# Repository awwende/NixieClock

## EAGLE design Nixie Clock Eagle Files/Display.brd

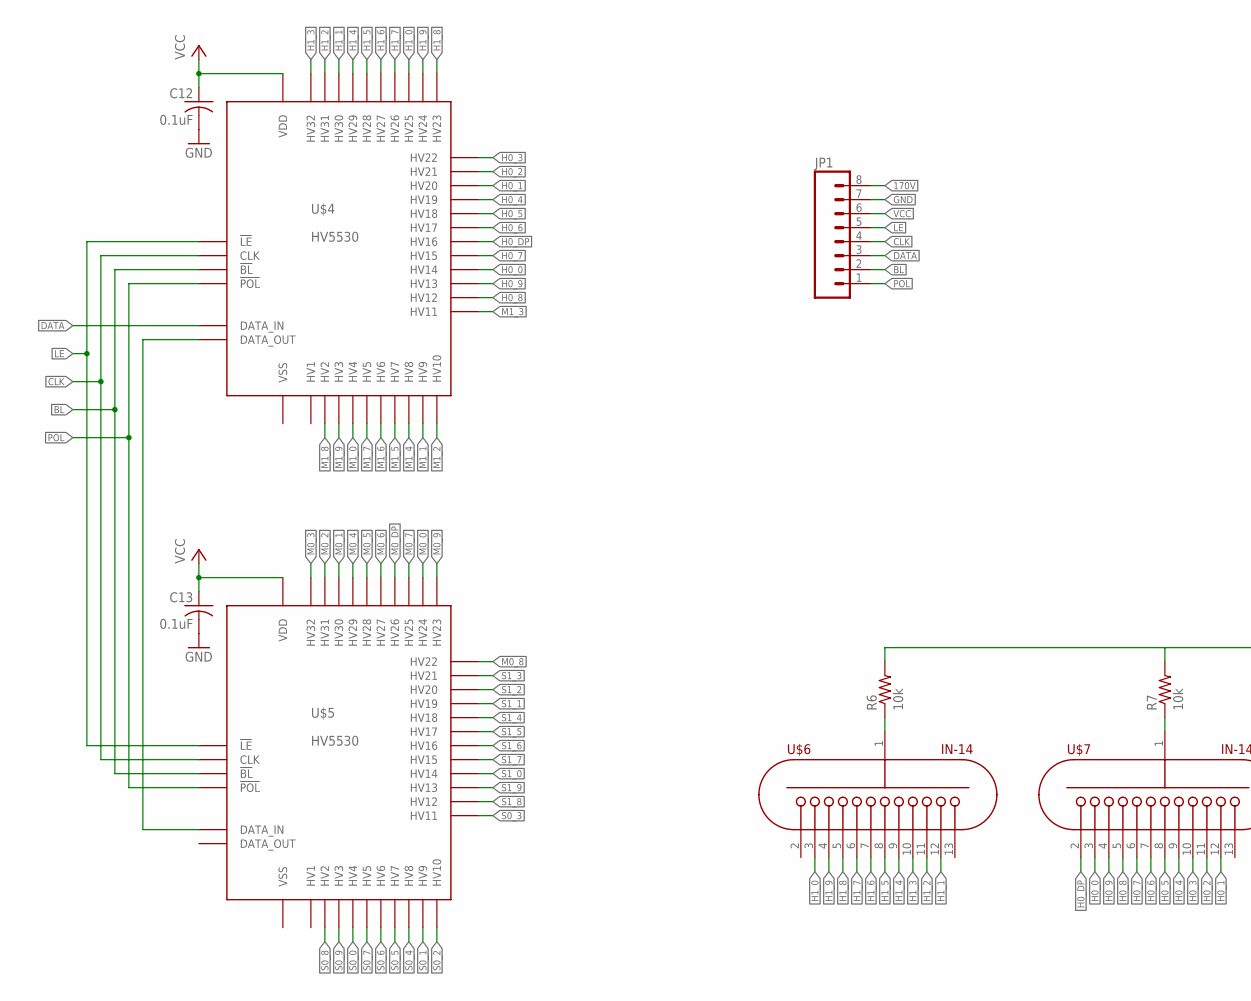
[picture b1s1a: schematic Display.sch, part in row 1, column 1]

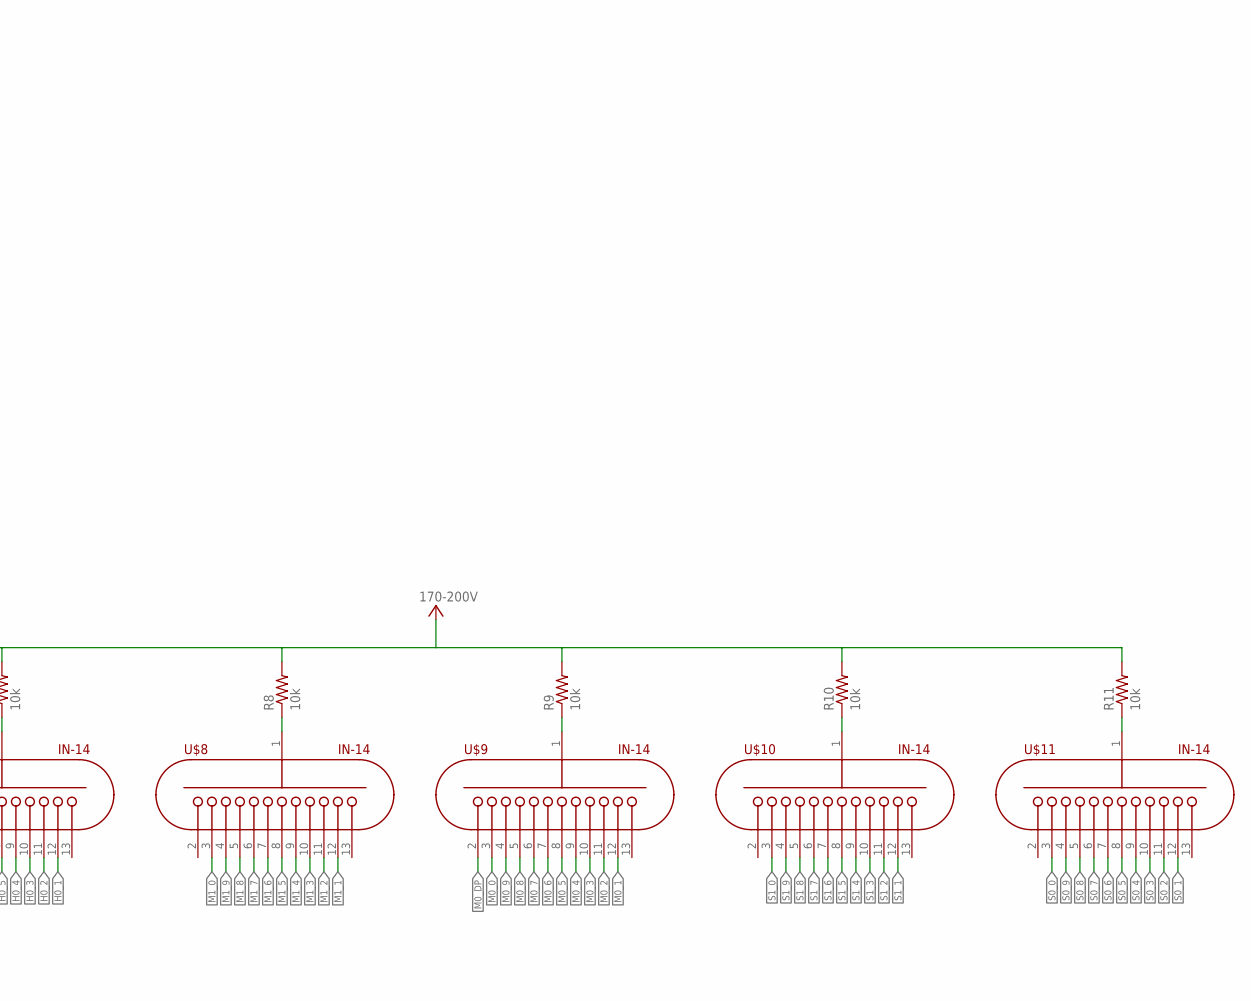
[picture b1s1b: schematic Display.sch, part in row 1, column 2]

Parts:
C12, C13: 0.1uF; C0603
JP1: M08; 1X08_PIN1_NO_SILK
R6, R7, R8, R9, R10, R11: 10k; R0603
U$4, U$5: HV5530PLCC; PLCC
U$6, U$7, U$8, U$9, U$10, U$11: IN-14

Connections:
170V: JP1.8, R6.2, R7.2, R8.2, R9.2, R10.2, R11.2
!BL: JP1.2, U$4.BL (!BL), U$5.BL (!BL)
!LE: JP1.5, U$4.LE (!LE), U$5.LE (!LE)
!POL: JP1.1, U$4.POL (!POL), U$5.POL (!POL)
CLK: JP1.4, U$4.CLK, U$5.CLK
DATA: JP1.3, U$4.D_IN (DATA_IN)
GND: C12.2, C13.2, JP1.7
H0_0: U$4.HV14, U$7.3
H0_1: U$4.HV20, U$7.12
H0_2: U$4.HV21, U$7.11
H0_3: U$4.HV22, U$7.10
H0_4: U$4.HV19, U$7.9
H0_5: U$4.HV18, U$7.8
H0_6: U$4.HV17, U$7.7
H0_7: U$4.HV15, U$7.6
H0_8: U$4.HV12, U$7.5
H0_9: U$4.HV13, U$7.4
H0_DP: U$4.HV16, U$7.2
H1_0: U$4.HV25, U$6.3
H1_1: U$4.HV30, U$6.12
H1_2: U$4.HV31, U$6.11
H1_3: U$4.HV32, U$6.10
H1_4: U$4.HV29, U$6.9
H1_5: U$4.HV28, U$6.8
H1_6: U$4.HV27, U$6.7
H1_7: U$4.HV26, U$6.6
H1_8: U$4.HV23, U$6.5
H1_9: U$4.HV24, U$6.4
M0_0: U$5.HV24, U$9.3
M0_1: U$5.HV30, U$9.12
M0_2: U$5.HV31, U$9.11
M0_3: U$5.HV32, U$9.10
M0_4: U$5.HV29, U$9.9
M0_5: U$5.HV28, U$9.8
M0_6: U$5.HV27, U$9.7
M0_7: U$5.HV25, U$9.6
M0_8: U$5.HV22, U$9.5
M0_9: U$5.HV23, U$9.4
M0_DP: U$5.HV26, U$9.2
M1_0: U$4.HV4, U$8.3
M1_1: U$4.HV9, U$8.12
M1_2: U$4.HV10, U$8.11
M1_3: U$4.HV11, U$8.10
M1_4: U$4.HV8, U$8.9
M1_5: U$4.HV7, U$8.8
M1_6: U$4.HV6, U$8.7
M1_7: U$4.HV5, U$8.6
M1_8: U$4.HV2, U$8.5
M1_9: U$4.HV3, U$8.4
unnamed: R6.1, U$6.1
unnamed: R9.1, U$9.1
unnamed: R10.1, U$10.1
unnamed: R11.1, U$11.1
unnamed: U$4.D_OUT (DATA_OUT), U$5.D_IN (DATA_IN)
unnamed: R7.1, U$7.1
unnamed: R8.1, U$8.1
S0_0: U$5.HV4, U$11.3
S0_1: U$5.HV9, U$11.12
S0_2: U$5.HV10, U$11.11
S0_3: U$5.HV11, U$11.10
S0_4: U$5.HV8, U$11.9
S0_5: U$5.HV7, U$11.8
S0_6: U$5.HV6, U$11.7
S0_7: U$5.HV5, U$11.6
S0_8: U$5.HV2, U$11.5
S0_9: U$5.HV3, U$11.4
S1_0: U$5.HV14, U$10.3
S1_1: U$5.HV19, U$10.12
S1_2: U$5.HV20, U$10.11
S1_3: U$5.HV21, U$10.10
S1_4: U$5.HV18, U$10.9
S1_5: U$5.HV17, U$10.8
S1_6: U$5.HV16, U$10.7
S1_7: U$5.HV15, U$10.6
S1_8: U$5.HV12, U$10.5
S1_9: U$5.HV13, U$10.4
VCC: C12.1, C13.1, JP1.6, U$4.VDD, U$5.VDD

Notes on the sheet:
HV5530

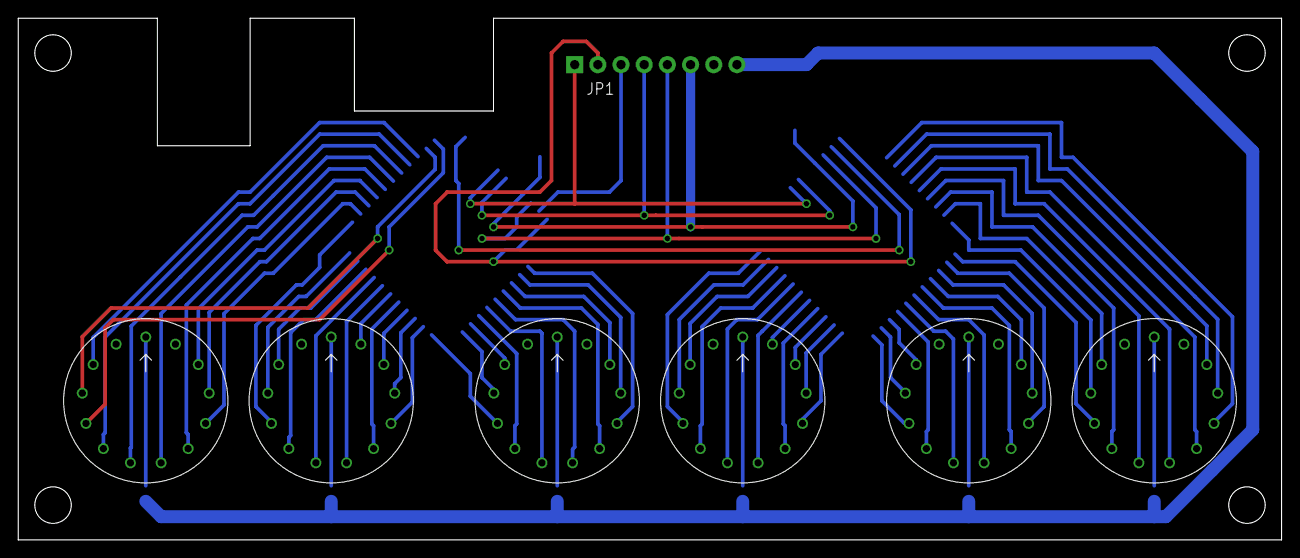
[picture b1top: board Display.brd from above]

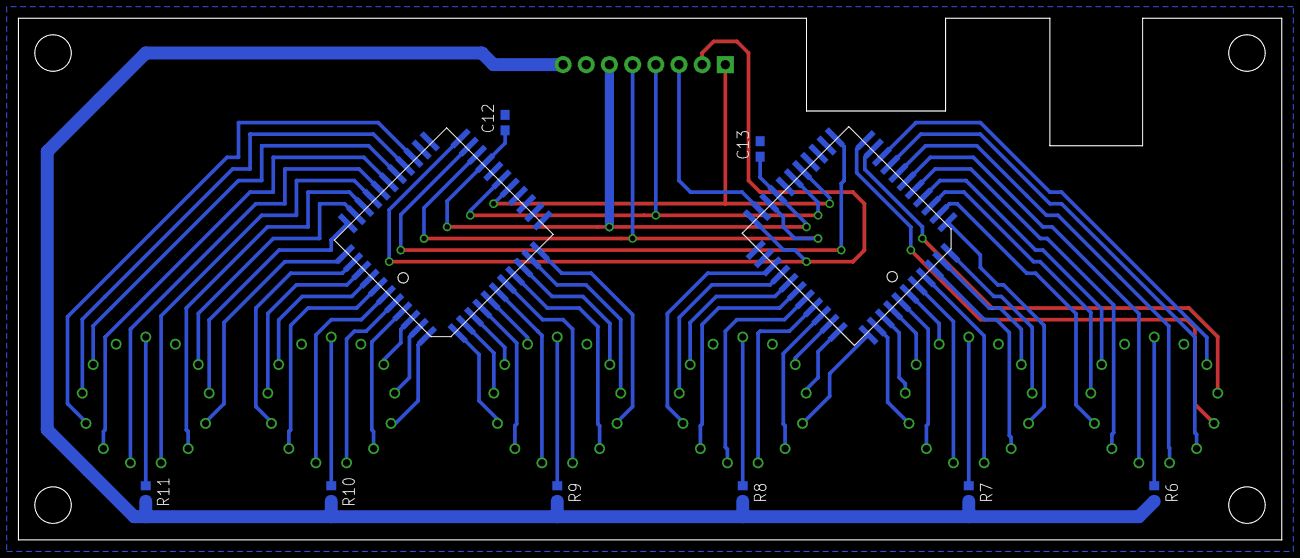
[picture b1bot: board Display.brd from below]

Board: 2 copper layers, 138.4 x 57.1 mm, 17 parts (10 on the bottom side), 77 nets.

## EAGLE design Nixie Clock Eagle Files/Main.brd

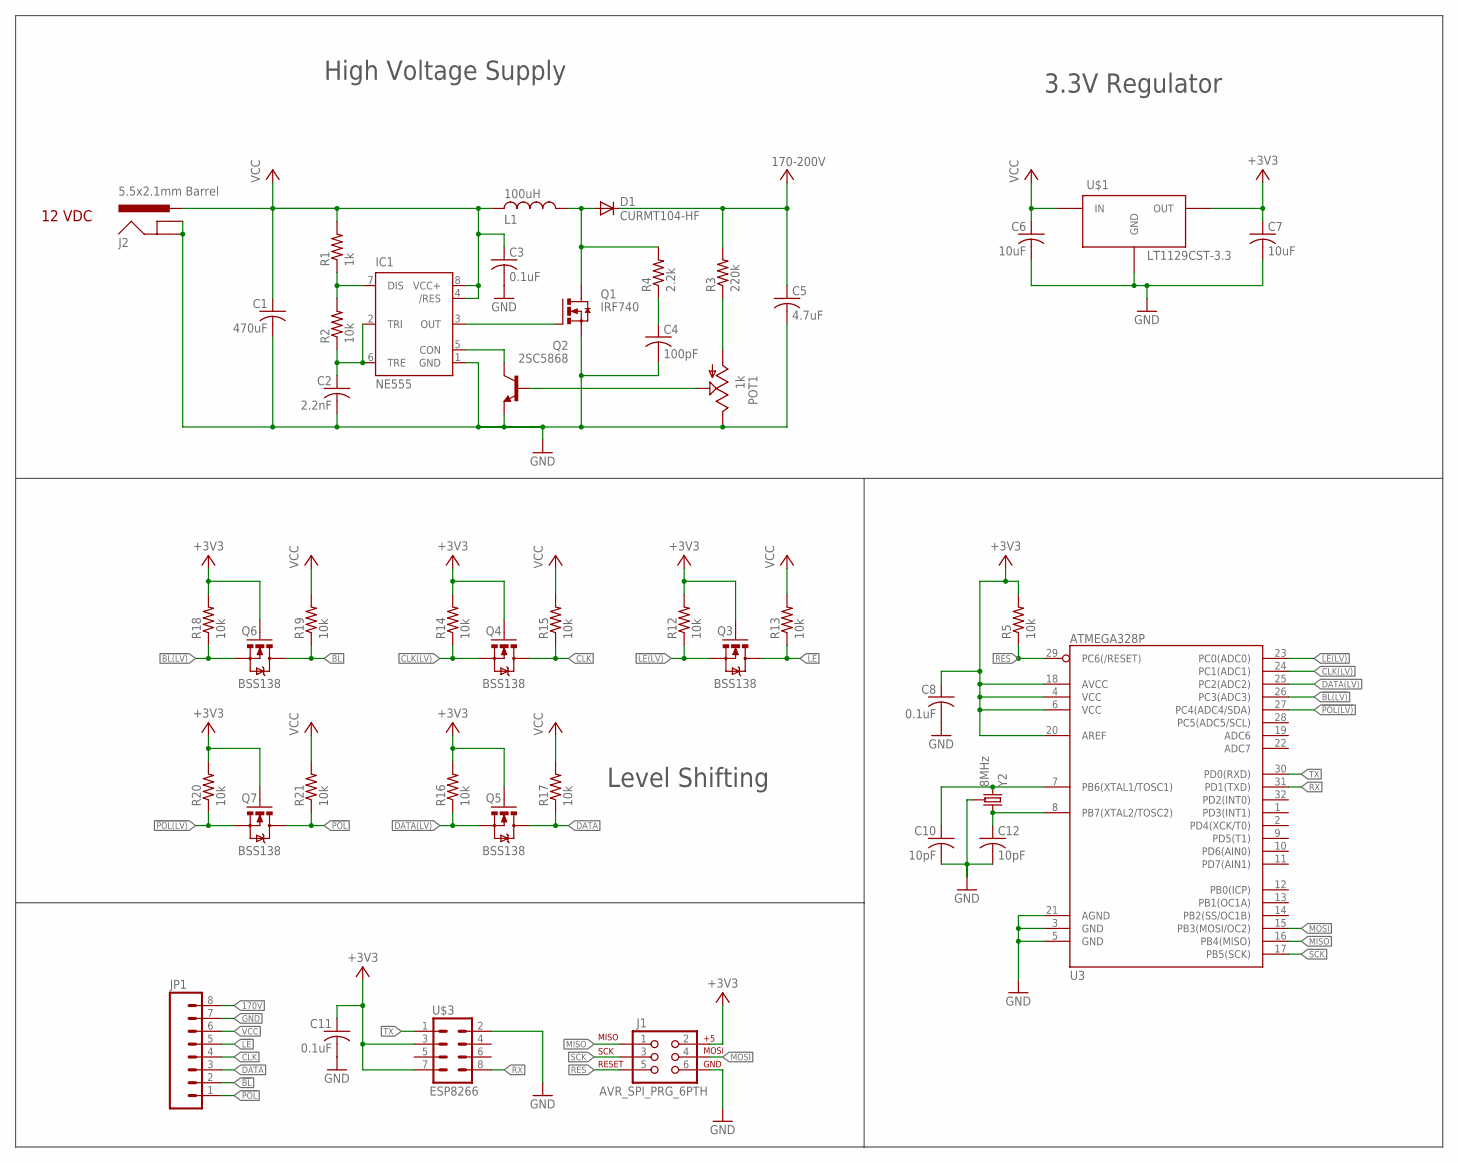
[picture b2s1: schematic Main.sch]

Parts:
C1: 470uF; C0603
C2: 2.2nF; C0603
C3, C8, C11: 0.1uF; C0603
C4: 100pF; C0603
C5: 4.7uF; C0603
C6, C7: 10uF; C0603
C10, C12: 10pF; C0603
D1: CURMT104-HF; SOD-123_MINI-SMA
IC1: NE555; SO08
J1: AVR_SPI_PRG_6PTH; 2X3
J2: 5.5x2.1mm Barrel; POWER_JACK_SMD
JP1: M08; 1X08_PIN1_NO_SILK
L1: 100uH; L2012C
POT1: 1k; 1X03
Q1: IRF740; D2PACK
Q2: 2SC5868; SOT23-BEC
Q3, Q4, Q5, Q6, Q7: BSS138; SOT23
R1: 1k; R0603
R2, R5, R12, R13, R14, R15, R16, R17, R18, R19, R20, R21: 10k; R0603
R3: 220k; R0603
R4: 2.2k; R0603
U3: ATMEGA328P; TQFP32-08
U$1: LT1129CST-3.3; SOT-223
U$3: ESP8266; 2X4
Y2: 8MHz; CTS406

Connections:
170V: C5.1, D1.C, JP1.8, R3.2
!BL: JP1.2, Q6.3 (D), R19.1
!BL(LV): Q6.2 (S), R18.1, U3.26 (PC3(ADC3))
!LE: JP1.5, Q3.3 (D), R13.1
!LE(LV): Q3.2 (S), R12.1, U3.23 (PC0(ADC0))
!POL: JP1.1, Q7.3 (D), R21.1
!POL(LV): Q7.2 (S), R20.1, U3.27 (PC4(ADC4/SDA))
+3V3: C7.1, C8.1, C11.1, J1.2, Q3.1 (G), Q4.1 (G), Q5.1 (G), Q6.1 (G), Q7.1 (G), R5.2, R12.2, R14.2, R16.2, R18.2, R20.2, U3.4 (VCC), U3.6 (VCC), U3.18 (AVCC), U3.20 (AREF), U$1.VOUT (OUT), U$3.3, U$3.7
CLK: JP1.4, Q4.3 (D), R15.1
CLK(LV): Q4.2 (S), R14.1, U3.24 (PC1(ADC1))
DATA: JP1.3, Q5.3 (D), R17.1
DATA(LV): Q5.2 (S), R16.1, U3.25 (PC2(ADC2))
GND: C1.2, C2.2, C3.2, C4.2, C5.2, C6.2, C7.2, C8.2, C10.2, C11.2, C12.2, IC1.1 (GND), J1.6, J2.GND (GNDBREAK), J2.P$4 (GND), JP1.7, POT1.3 (E), Q1.3 (S), Q2.E, U3.3 (GND), U3.5 (GND), U3.21 (AGND), U$1.GND, U$1.GND1 (GND), U$3.2, Y2.2 (GND), Y2.4 (GND)
MISO: J1.1, U3.16 (PB4(MISO))
MOSI: J1.4, U3.15 (PB3(MOSI/OC2))
unnamed: C2.1, IC1.2 (TRI), IC1.6 (TRE), R2.1
unnamed: C12.1, U3.8 (PB7(XTAL2/TOSC2)), Y2.1
unnamed: IC1.7 (DIS), R1.1, R2.2
unnamed: C10.1, U3.7 (PB6(XTAL1/TOSC1)), Y2.3 (2)
unnamed: IC1.3 (OUT), Q1.1 (G)
unnamed: D1.A, L1.1, Q1.2 (D), R4.2
unnamed: C4.1, R4.1
unnamed: POT1.1 (A), R3.1
unnamed: IC1.5 (CON), Q2.C
POT1: POT1.2 (S), Q2.B
RES: J1.5, R5.1, U3.29 (PC6(/RESET))
RX: U3.31 (PD1(TXD)), U$3.8
SCK: J1.3, U3.17 (PB5(SCK))
TX: U3.30 (PD0(RXD)), U$3.1
VCC: C1.1, C3.1, C6.1, IC1.4 (/RES), IC1.8 (VCC+), J2.VIN0 (PWR), JP1.6, L1.2, R1.2, R13.2, R15.2, R17.2, R19.2, R21.2, U$1.VIN (IN)

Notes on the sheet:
12 VDC
Level Shifting
High Voltage Supply
3.3V Regulator

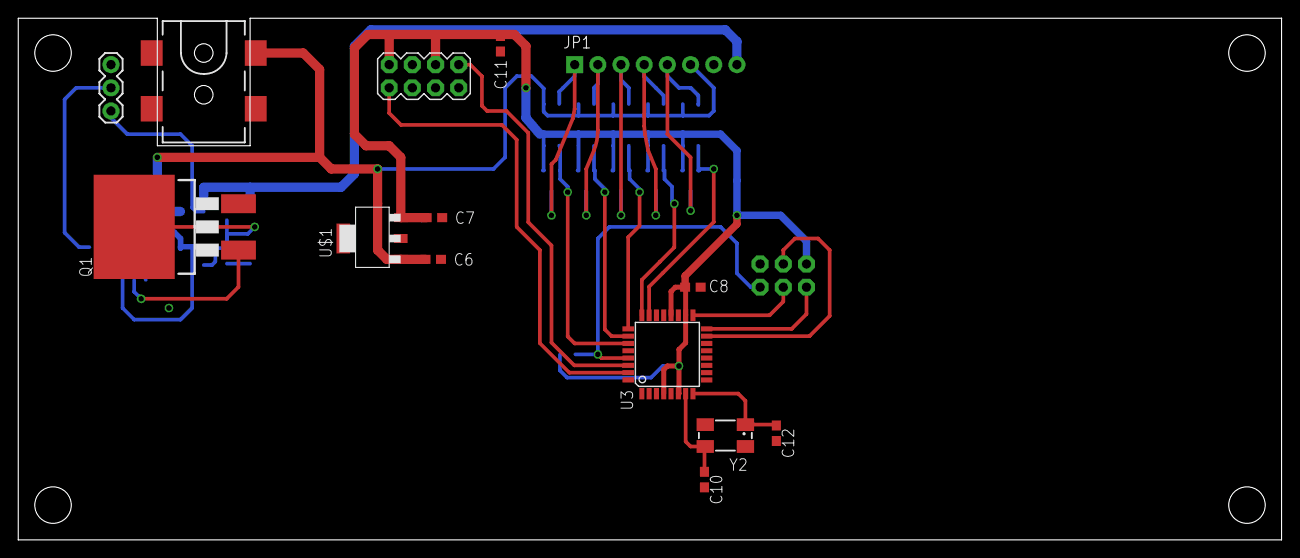
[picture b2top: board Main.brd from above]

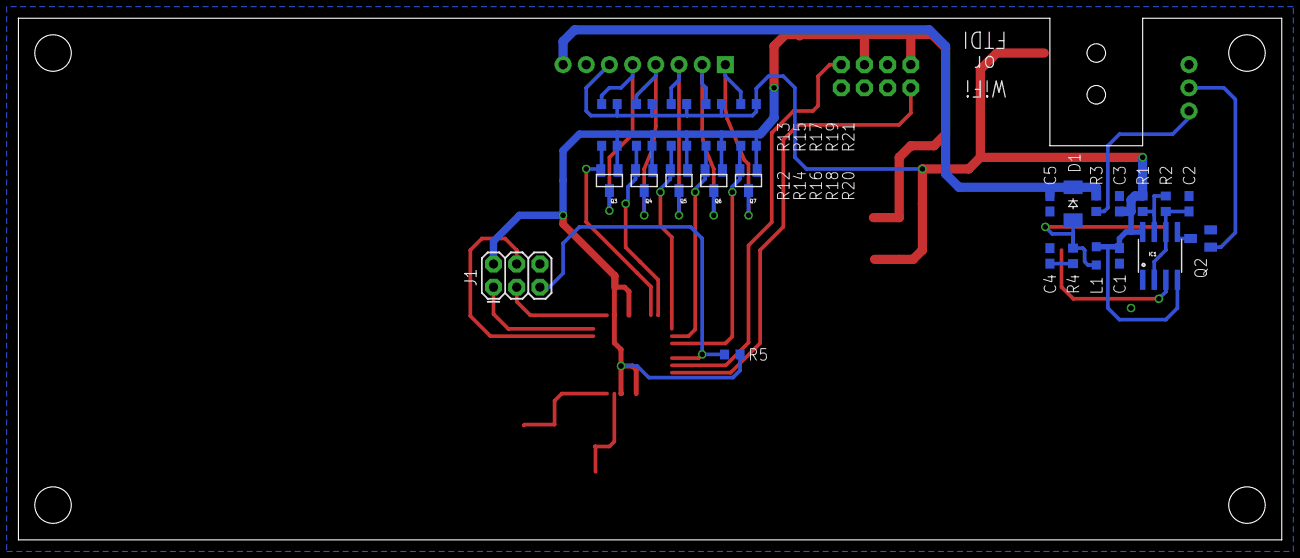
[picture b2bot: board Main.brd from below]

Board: 2 copper layers, 138.4 x 57.1 mm, 44 parts (30 on the bottom side), 30 nets.

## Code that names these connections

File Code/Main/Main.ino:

#include <Time.h>
#include <avr/io.h>
#include <util/delay.h>;
#include <avr/interrupt.h>
#include <avr/wdt.h>
#include <EEPROM.h>

#define sr_le     PC0  //Latch Enable
#define sr_clk    PC1  //Clock
#define sr_dataIN PC2  //Data Input
#define sr_bl     PC3  //Blanking (0:OFF, 1:ON)
#define sr_pol    PC4  //Polarity (0:Invert 1: Normal)

String lastMessageReceived="";
String lastMessageSent="";
String ssid, pw;
byte ip[4];
int timeOffset;
boolean wifiConnected=false, updated=false;

void setup() 
{
  //Setup watchdog Timer
  WDTCSR |= (1<<WDCE)|(1<<WDE);
  WDTCSR = (1<<WDE)|(1<<WDP2) |(1<<WDP1);
  wdt_reset();

  Serial.begin(9600);
  //Wait 2 seconds for ESP8266 to Start
  for(byte i=0;i<8;i++)
  {
    wdt_reset();
    _delay_ms(250);
  }
  //Setup Shift Register
  DDRC |= (1<<sr_le) | (1<<sr_clk) | (1<<sr_dataIN) | (1<<sr_bl) | (1<<sr_pol);
  PORTC |= (1<<sr_bl) | (1<<sr_pol);
  
  //Serial.println("Started");
  wifi_setup();
  //Serial.println(String(hour())+":"+String(minute())+":"+String(second()));
}

void loop()
{
  byte myHour = hour();
  byte myMin = minute();
  byte mySec = second();
  byte digit[6] = {0};  //Array of clock digits
  check_serial();
  wdt_reset();
  if(myHour==23 && myMin==0 && mySec==0){ //Wait for WDT to reset microcontroller (Update the time)
    Serial.println("RS");
    while(1){}   
  }
  if(myHour > 12) myHour -= 12;
  else if(myHour == 0) myHour = 12;

  if(myHour<10)digit[5]=0;
  else digit[5] = myHour/10;
  digit[4] = myHour%10;
  
  if(myMin<10)digit[3]=0;
  else digit[3] = myMin/10;
  digit[2] = myMin%10;

  if(mySec<10)digit[1]=0;
  else digit[1] = mySec/10;
  digit[0] = mySec%10;
  
  for(byte i=0;i<6;i++){    //Display the digits on the nixies
    display_digit(i,digit[i]);
  }
}

String check_serial(){
  String message = "";
  byte failCount = 0;

  if(Serial.available()){
    _delay_ms(20);
    while(Serial.available()){
      message += char(Serial.read());
      _delay_ms(1);
    }
    if(message.startsWith("ACK ")){
      if(message.charAt(6) == ':'){
        byte hourTemp = (message.charAt(4)-48)*10 + (message.charAt(5)-48);
        byte minTemp  = (message.charAt(7)-48)*10 + (message.charAt(8)-48);
        byte secTemp  = (message.charAt(10)-48)*10 + (message.charAt(11)-48) + 1;
        setTime(hourTemp,minTemp,secTemp,1,1,1);
      }
    }
    else if(message.startsWith("RESET")){
      while(1){}
    }
  }
  else message = "";
  return message;
}

void sendMessage(String message){
  Serial.println(message);
  lastMessageSent = message;
  _delay_ms(50);
  wdt_reset();
}

void display_digit(byte digit, byte value){
  //When time is HH:MM:SS, digit flows left to right (including ":") valid 
  //and can be 0-7
  //value is the value to display on the element (0-9)
  const byte LUT[] = {2,7,8,9,6,5,4,3,0,1};   //Array takes 0-10, where 0-9 are the dec digit and 10 is the DP
  const byte srOffset[] = {32,43,53,0,11,22}; //How many 0s lead in the array to be clocked into Shift Register (SR)
  boolean srBuffer[65] = {0};
  if(value<10)  srBuffer[srOffset[digit]+LUT[value]+1]=1;      //Set SR bit
  PORTC &= ~(1<<sr_le);                          //Disable the SR latch
  for(byte i=64;i>0;i--){                        //Clock in all 64-bits of data to SR
    PORTC |= (1<<sr_clk);
    if(srBuffer[i]) PORTC |= (1<<sr_dataIN);
    else PORTC &= ~(1<<sr_dataIN);
    _delay_us(10);
    PORTC &= ~(1<<sr_clk);
    _delay_us(10);
  }
  PORTC |= (1<<sr_le);
  //digitalWrite(A0,HIGH);                          //Enable the SR latch to illuminate digit
  _delay_us(250);                                       //Wait 5ms, so that your eyes can actually see it
}

void wifi_setup(){
  String message="";
  display_digit(0,0);   //Configure NTP IP address
  while(!message.startsWith("ACK 7") && !message.startsWith("ACK 8")){ //Get Status
    wdt_reset();
    Serial.println("ST");
    _delay_ms(200);
    message = check_serial();
  }
  message = message.substring(4);
  if(message.startsWith("8")){  //Connected to WiFi
    display_digit(0,4);
    for(byte i=0;i<5;i++){
      while(!message.startsWith("ACK ")){ //Get Time
        wdt_reset();
        Serial.println("GT");
        _delay_ms(200);
        message = check_serial();
      }
      message = message.substring(4);
      if(message.charAt(2) == ':') break;
    }
    if(message.startsWith("64")){
      display_digit(0,6);
      for(byte i=0;i<4;i++){
        wdt_reset();
        _delay_ms(250);
      }
    }
  }
  else{ //Not Connected
    if(message.startsWith("6") || message.startsWith("7")){
      display_digit(0,1);
      while(!message.startsWith("ACK 9")){ //Get Status
        wdt_reset();
        Serial.println("BG");
        _delay_ms(200);
        message = check_serial();
      }
      display_digit(0,2);
      while(!message.startsWith("ACK 7") && !message.startsWith("ACK 8")){ //Get Status
        wdt_reset();
        Serial.println("ST");
        _delay_ms(200);
        message = check_serial();
      }
      display_digit(0,3);
      message = message.substring(4);
      if(message.startsWith("8")){
        display_digit(0,4);
        for(byte i=0;i<5;i++){
          while(!message.startsWith("ACK ")){ //Get Time
            wdt_reset();
            Serial.println("GT");
            _delay_ms(200);
            message = check_serial();
          }
          message = message.substring(4);
          if(message.charAt(2) == ':') break;
        }
        if(message.startsWith("64")){
          display_digit(0,6);
          for(byte i=0;i<4;i++){
            wdt_reset();
            _delay_ms(250);
          }
        }
      }
      else{
        display_digit(0,5);
        while(1){} //reset
      }
    }
  }
}

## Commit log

2015-11-16 :boom::camel: Added .gitattributes & .gitignore files
2015-11-16 Initial Release
2015-11-16 Removed unnecessary files

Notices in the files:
parts and their libraries:
SparkFun-Connectors: Licensing: Creative Commons ShareAlike 4.0 International - https://creativecommons.org/licenses/by-sa/4.0
